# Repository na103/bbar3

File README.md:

# Big Box Amiga Action Replay III remake

This repository contains the reverse engineering schematic for the Amiga Action Replay III and everything needed to build it.<br>
<br>

<br>
<br>

## Board bill of materials
| Qt. |    Description     |             Designator          |    Mouser part     |             Note              |
|:---:|--------------------|---------------------------------|--------------------|-------------------------------|
|6    |Resistor 1K         |R1-R4, R6, R7                    |CRCW12061K00FKEA    |                               |
|17   |Resistor 4.7K       |R5, R8-R23                       |CRCW12064K70FKEA    |                               |
|1    |Cap. 10uF 16V       |C1                               |EEA-FC1E100H        |                               |
|4    |Cap. 100nf          |C2-C5                            |C1206C104K5RAC7867  |                               |
|1    |Cap. 1uF 63V        |C6                               |ESS105M050AB2AA     |                               |
|5    |GAL16V8             |U1-U5                            |ATF16V8BQL-15JU     |                               | 
|5    |PLCC 20 POS Socket  |U1-U5                            |540-88-020-17-400-TR| Optional                      |
|1    |74F74               |U6                               |SN74LS74ANSR        |                               |
|2    |27C010 OTP EPROM    |U7, U9                           |AT27C010-70JU-T     |                               |
|1    |SRAM 64K            |U8                               |AS6C6264-55SCN      |                               |
|1    |SRAM 256K           |U10                              |AS6C62256-55SCN     |                               |
|1    |MC1455              |U11                              |MC1455DR2G          |                               |
|2    |ZVP2106A            |Q1, Q2                           |ZVP2106A            |                               |
|1    |Diode               |D3                               |LL4148-M-18         |                               |
|1    |2.54MM 10P VERT HDR |J1                               |70246-1004          |                               |
|1    |SPDT ON-ON switch   |SW1                              |MHSS1104            |                               |

## Remote control bill of materials
| Qt. |    Description     |             Designator          |    Mouser part     |             Note              |
|:---:|--------------------|---------------------------------|--------------------|-------------------------------|
|1    |Trimmer 10K         |VR1                              |RV09AF-40-20K-B10K  |                               |
|1    |Button switch red   |SW1                              |D6C40F1LFS          |                               |
|1    |SPDT ON-ON switch   |SW2                              |2MS1T1B3M2QES       |                               |
|1    |IDC 10pos F cable   |                                 |                    | available on amazon           |
|1    |2.54MM 10P VERT HDR |J1                               |70246-1004          |                               |

<br><br>

If you found this my work useful, please consider buying me a cup of coffee if you want:<br>

# License

This work is licensed under a Creative Commons Attribution 4.0 International License. See [https://creativecommons.org/licenses/by/4.0/](https://creativecommons.org/licenses/by/4.0/).

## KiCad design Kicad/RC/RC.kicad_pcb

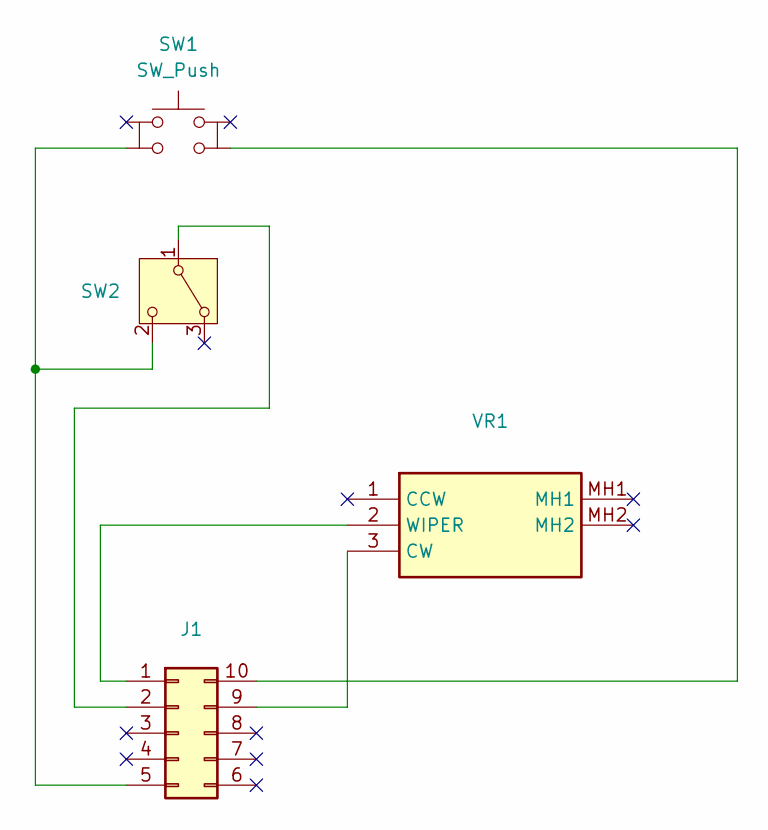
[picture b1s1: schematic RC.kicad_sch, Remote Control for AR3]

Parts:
J1: PinHeader_2x05_P2.54mm_Vertical
SW1: SW_Push; SW_Push_2P1T_Toggle_CK_PVA1xxH1xxxxxxV3
SW2: SW_Wuerth_450301014042; SW_Slide-03_Wuerth-WS-SLTV_10x2.5x6.4_P2.54mm
VR1: RV09AF-40-20K-B1M; RV09AF4020KB1M; Mouser Part Number 317-2090F-1M

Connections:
unnamed: J1.1, VR1.2 (WIPER)
unnamed: J1.2, SW2.1 (B)
unnamed: J1.5, SW1.3, SW2.2 (C)
unnamed: J1.9, VR1.3 (CW)
unnamed: J1.10, SW1.4

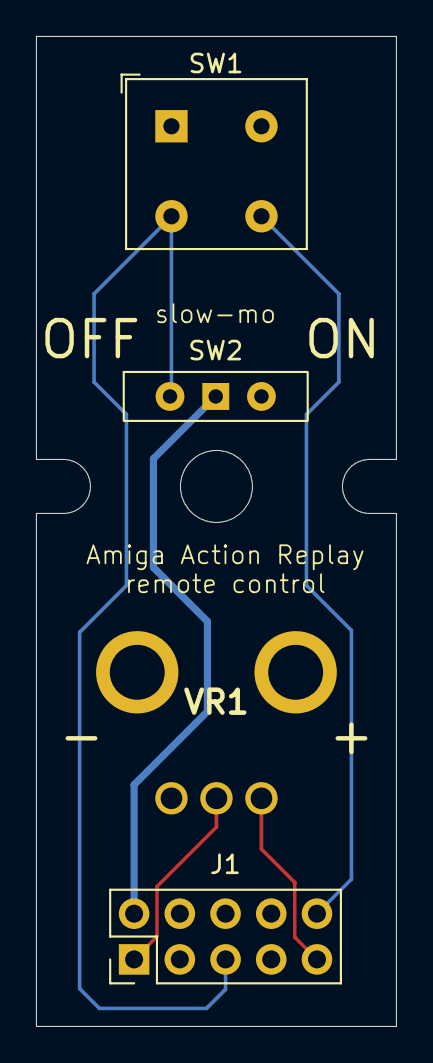
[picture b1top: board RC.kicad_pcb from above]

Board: 2 copper layers, 20.0 x 55.0 mm, 4 parts (0 on the bottom side), 5 nets.

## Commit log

2025-02-02 GAL jed files
2025-02-02 Kicad projects
2025-02-02 original PAL jed files
2025-02-02 ROM files
2025-02-02 readme and license
2025-02-04 label update
2025-02-14 update SW1 footprint
2025-02-18 U3 PAL jed corrected
